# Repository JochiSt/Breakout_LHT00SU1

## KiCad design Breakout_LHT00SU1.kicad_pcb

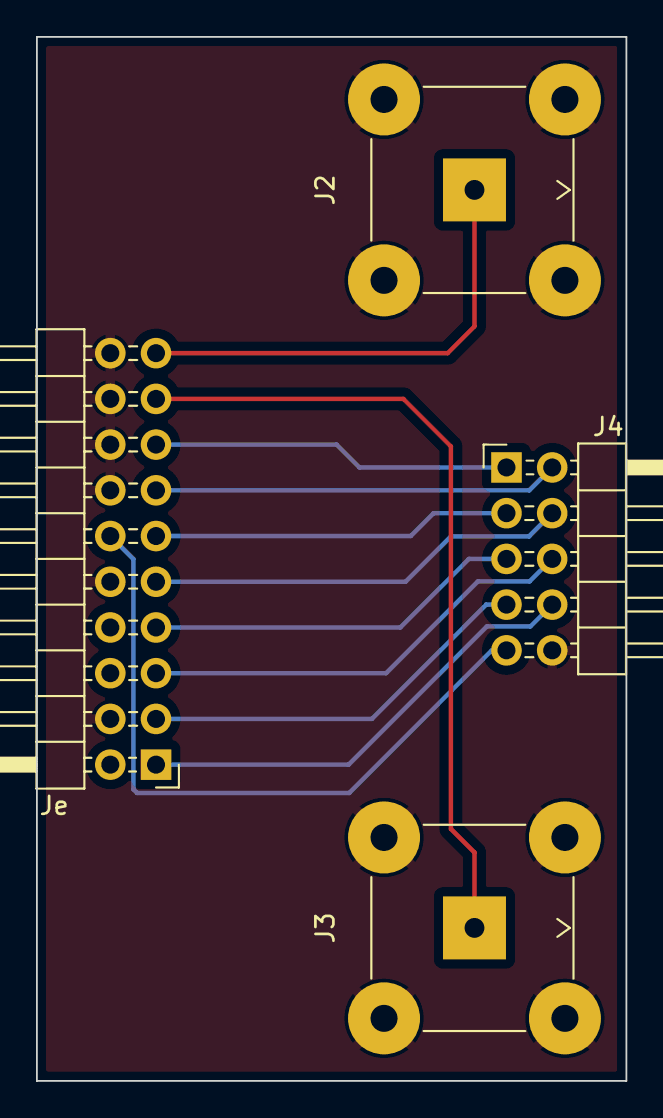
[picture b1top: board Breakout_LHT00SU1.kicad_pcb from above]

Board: 2 copper layers, 32.8 x 58.0 mm, 4 parts (0 on the bottom side), 12 nets.

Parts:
J2, J3: Conn_Coaxial; BNC_TEConnectivity_1478035_Horizontal
J4: Conn_02x05_Odd_Even; PinHeader_2x05_P2.54mm_Horizontal
Je: Conn_02x10_Odd_Even; PinHeader_2x10_P2.54mm_Horizontal

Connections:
/1ACH: J2.1 (In), Je.19
/1DCH: J4.1, Je.15
/2ACH: J3.1 (In), Je.17
/2DCH: J4.2, Je.13
/3DCH: J4.3, Je.11
/4DCH: J4.4, Je.9
/5DCH: J4.5, Je.7
/6DCH: J4.6, Je.5
/7DCH: J4.7, Je.3
/8DCH: J4.8, Je.1
/CLK: J4.9, Je.12
/GND: J2.2 (Ext), J3.2 (Ext), J4.10, Je.4, Je.10, Je.14, Je.16, Je.18, Je.20

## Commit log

2022-10-21 added KiCAD project
    containing empty PCB
2022-10-21 added schematic with LHT00SU1 pinout
2022-12-02 added 2x5 header + 2x BNC
    output for digital signals and analog inputs
2022-12-02 updated layout (first iteration done)
    done with first iteration, needs some improvements in order to save PCB space...
